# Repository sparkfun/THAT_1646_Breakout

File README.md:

SparkFun THAT 1646 Breakout
========================================

[*BOB-14003*](https://www.sparkfun.com/products/14003)

The THAT 1646 OutSmarts Breakout Board offers an easy solution to adding a balanced audio output to your circuits. The THAT OutSmarts technology has been designed as a high-grade analog line driver and offers a low distortion and high common mode rejection in real-world audio applications. Each breakout board combines the THAT 1646 IC, its supporting components and a ¼" TRS (Tip Ring Sleeve) socket. With these powers combined, you will find it very easy to use the output drivers on breadboards and in projects!

The THAT 1646 OutSmarts Breakout and its sibling, the THAT 1206 InGenius Breakout, perform mirror-image signal conversion. While the InGenius is a balanced-to-unbalanced input receiver, this OutSmarts is an unbalanced-to-balanced output driver. We have made sure to break out each pin you need to utilize the OutSmarts board including the unbalanced input (IN), the positive and negative power supply rails (V+, V-) and, of course, ground (GND). Additionally, adjacent to each leg of the socket are test points for the signal (T, R, S) and normal (TN, RN, SN) contacts.

Repository Contents
-------------------

* **/Hardware** - Eagle design files (.brd, .sch)
* **/Production** - Production panel files (.brd)

Documentation
--------------
* **[Hookup Guide](https://learn.sparkfun.com/tutorials/that-ingenuis-and-outsmarts-breakout-hookup-guide)** - Basic hookup guide for the THAT 1206 and 1646 breakouts.
* **[SparkFun Fritzing repo](https://github.com/sparkfun/Fritzing_Parts)** - Fritzing diagrams for SparkFun products.
* **[SparkFun 3D Model repo](https://github.com/sparkfun/3D_Models)** - 3D models of SparkFun products.

Product Versions
----------------
* [BOB-14003](https://www.sparkfun.com/products/14003) - THAT 1646 OutSmarts breakout board.
* [BOB-14002](https://www.sparkfun.com/products/14002) - The companion THAT 1206 InGenius breakout board.

Version History
---------------
* [V1.0 Tag](https://github.com/sparkfun/THAT_1646_Breakout/commit/2f91aec23e70d395754cfb3aa0515f236956341f) - Files as of product launch.

License Information
-------------------

This product is _**open source**_!

Please review the LICENSE.md file for license information.

If you have any questions or concerns on licensing, please contact techsupport@sparkfun.com.

Distributed as-is; no warranty is given.

- Your friends at SparkFun.

_<COLLABORATION CREDIT>_

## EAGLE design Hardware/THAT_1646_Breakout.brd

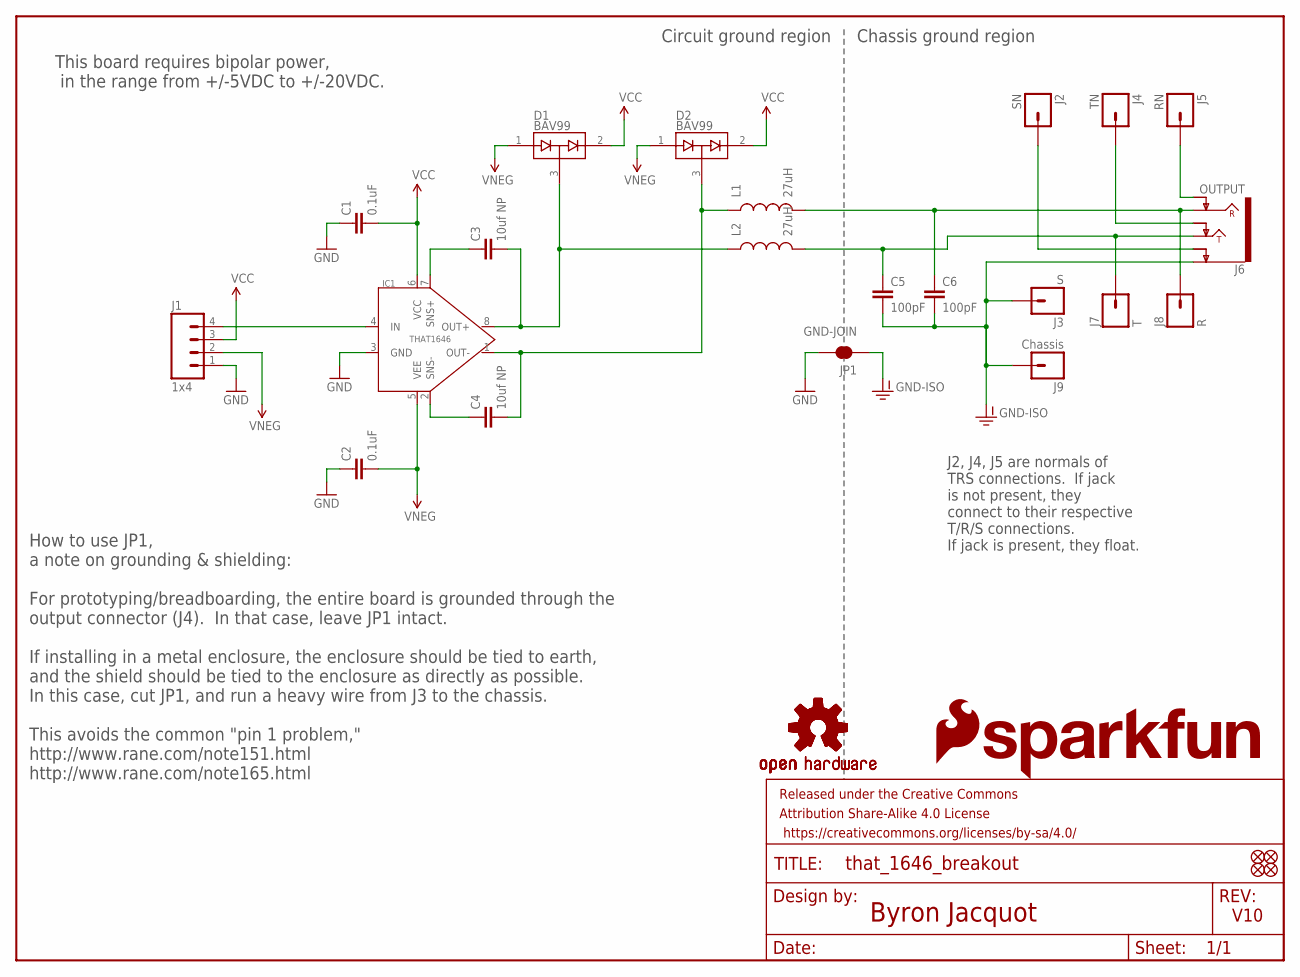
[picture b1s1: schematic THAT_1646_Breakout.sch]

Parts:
C1, C2: 0.1uF; 0603-CAP
C3, C4: 10uf NP; PANASONIC_D
C5, C6: 100pF; 0603-CAP
D1, D2: BAV99; SOT23-3
FD1, FD2, FD3, FD4: FIDUCIALUFIDUCIAL; MICRO-FIDUCIAL
FRAME1: FRAME-LETTER; CREATIVE_COMMONS
IC1: THAT1646; SO08
J1: 1x4; 1X04_NO_SILK_ALL_ROUND
J2: SN; 1X01_NO_SILK
J3: S; 1X01_NO_SILK
J4: TN; 1X01_NO_SILK
J5: RN; 1X01_NO_SILK
J6: OUTPUT; AUDIO_JACK_0.25"_TRS_PTH_RA
J7: T; 1X01_NO_SILK
J8: R; 1X01_NO_SILK
J9: Chassis; 1X01_NO_SILK
JP1: GND-JOIN; PAD-JUMPER-2-NC_BY_TRACE_YES_SILK
L1, L2: 27uH; 0603
LOGO1, LOGO2: OSHW-LOGOS; OSHW-LOGO-S
LOGO4: SFE_LOGO_FLAME.2_INCH; SFE_LOGO_FLAME_.2
LOGO5: SFE_LOGO_NAME.1_INCH; SFE_LOGO_NAME_.1

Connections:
GND: C1.1, C2.1, IC1.3 (GND), J1.1, JP1.2
GND-ISO: C5.2, C6.2, J3.1, J6.SLEEVE (EARTH), J9.1, JP1.1
unnamed: J5.1, J6.RING-NORM
unnamed: J4.1, J6.TIP-NORM
unnamed: J2.1, J6.SLEEVE-NORM (EARTH-NORM)
unnamed: C5.1, J6.TIP, J7.1, L2.2
unnamed: C6.1, J6.RING, J8.1, L1.2
unnamed: C3.- (2), D1.3 (COM), IC1.8 (OUT+), L2.1
unnamed: C4.- (2), D2.3 (COM), IC1.1 (OUT-), L1.1
unnamed: C4.+ (1), IC1.2 (SNS-)
unnamed: C3.+ (1), IC1.7 (SNS+)
unnamed: IC1.4 (IN), J1.4
VCC: C1.2, D1.2 (C2), D2.2 (C2), IC1.6 (VCC), J1.3
VNEG: C2.2, D1.1 (A1), D2.1 (A1), IC1.5 (VEE), J1.2

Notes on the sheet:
Byron Jacquot
V10
Chassis ground region
Circuit ground region
How to use JP1, a note on grounding & shielding: For prototyping/breadboarding, the entire board is grounded through the output connector (J4). In that case, leave JP1 intact. If installing in a metal enclosure, the enclosure should be tied to earth, and the shield should be tied to the enclosure a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
This board requires bipolar power, in the range from +/-5VDC to +/-20VDC.
J2, J4, J5 are normals of TRS connections. If jack is not present, they connect to their respective T/R/S connections. If jack is present, they float.

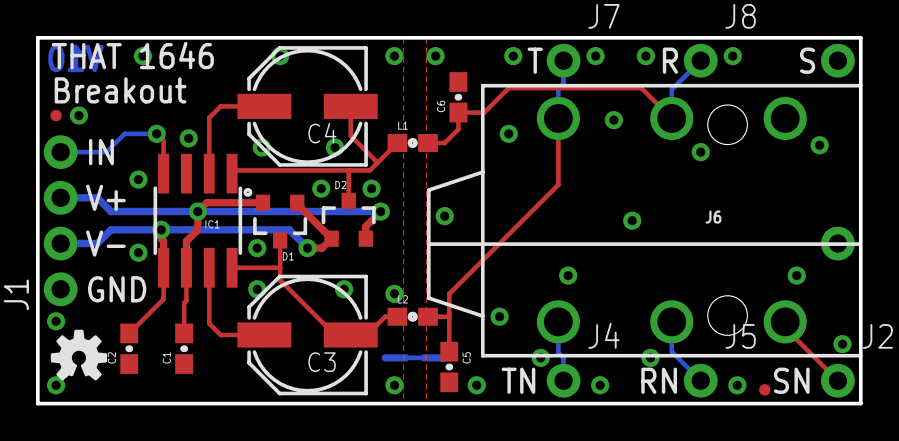
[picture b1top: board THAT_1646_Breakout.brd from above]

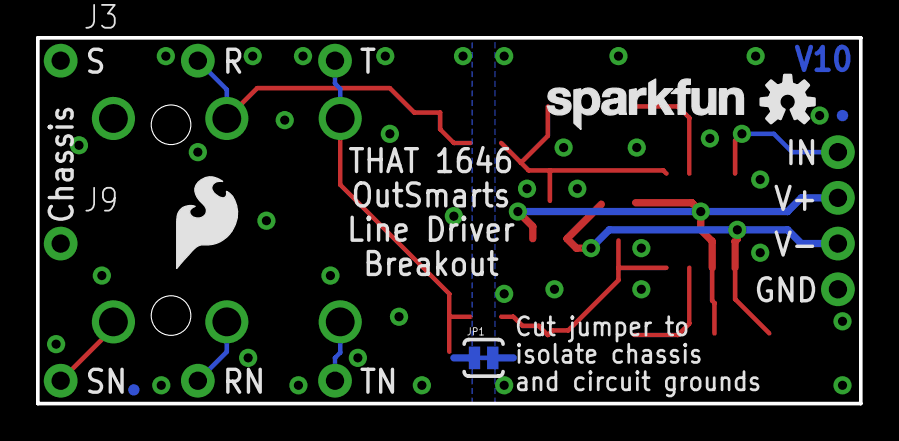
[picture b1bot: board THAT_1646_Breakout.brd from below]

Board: 2 copper layers, 45.7 x 20.3 mm, 30 parts (8 on the bottom side), 14 nets.

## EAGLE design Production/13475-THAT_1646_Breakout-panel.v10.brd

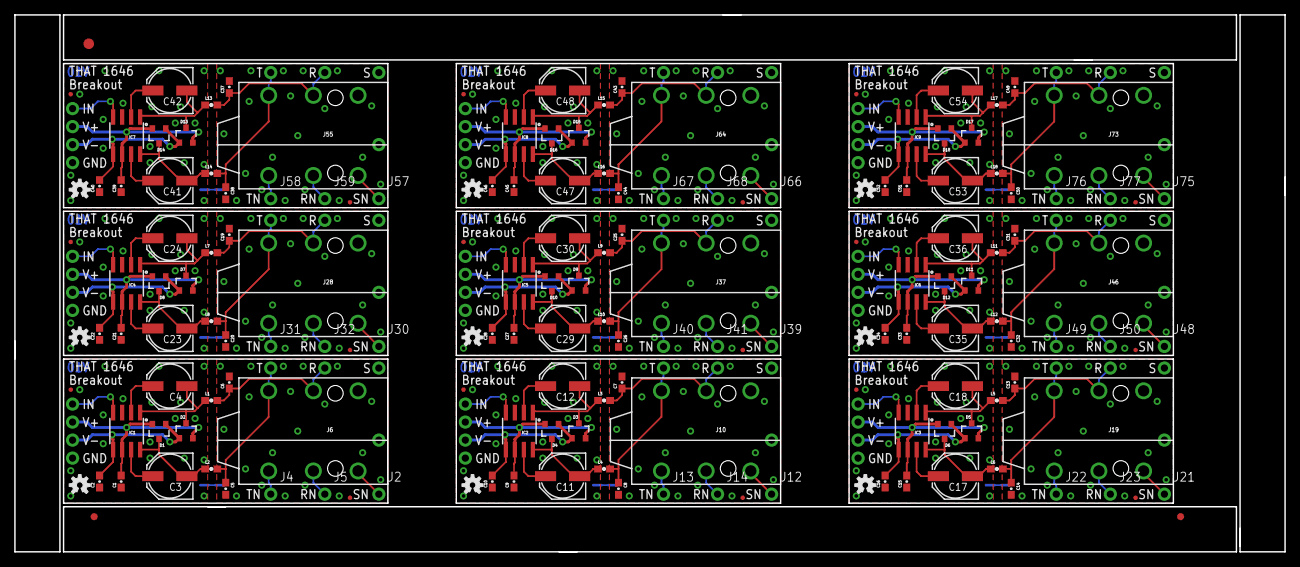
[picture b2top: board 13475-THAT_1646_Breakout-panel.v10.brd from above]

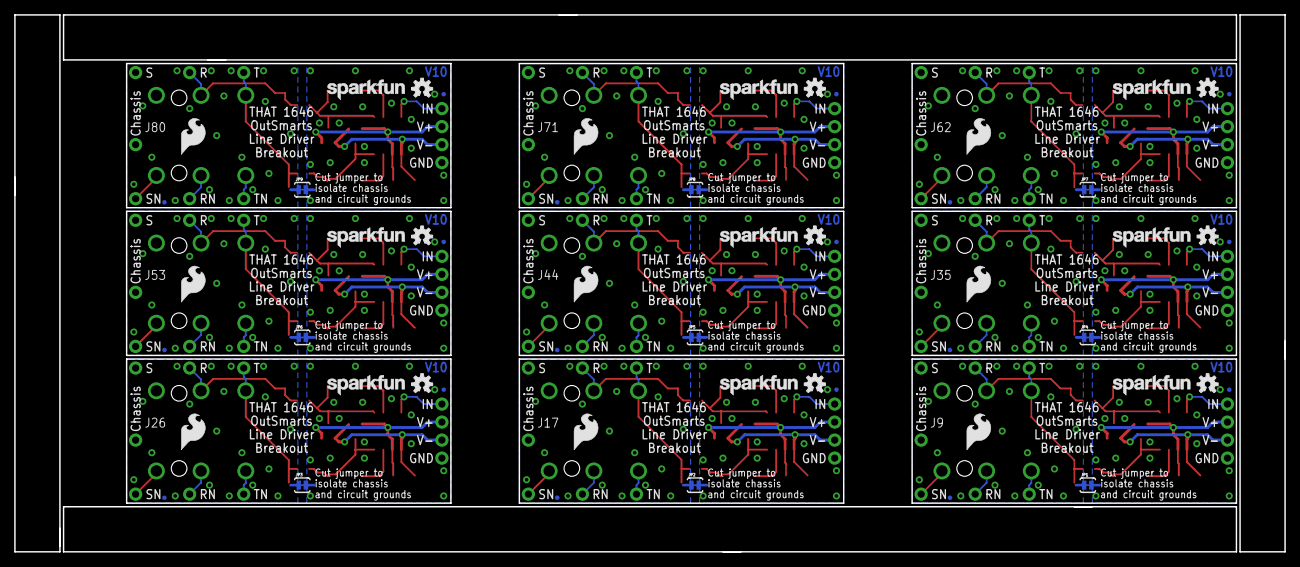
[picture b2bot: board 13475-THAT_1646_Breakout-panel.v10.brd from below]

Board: 2 copper layers, 179.1 x 75.7 mm, 264 parts (72 on the bottom side), 126 nets.

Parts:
C1, C2, C9, C10, C15, C16, C21, C22, C27, C28, C33, C34, C39, C40, C45, C46, C51, C52: 0.1uF; 0603-CAP
C3, C4, C11, C12, C17, C18, C23, C24, C29, C30, C35, C36, C41, C42, C47, C48, C53, C54: 10uf NP; PANASONIC_D
C5, C6, C7, C8, C13, C14, C19, C20, C25, C26, C31, C32, C37, C38, C43, C44, C49, C50: 100pF; 0603-CAP
D1, D2, D3, D4, D5, D6, D7, D8, D9, D10, D11, D12, D13, D14, D15, D16, D17, D18: BAV99; SOT23-3
E$1: FIDUCIAL-1.5X3
E$3, E$4: FIDUCIAL-1X2
FD1, FD2, FD3, FD4, FD5, FD6, FD7, FD8, FD9, FD10, FD11, FD12, FD13, FD14, FD15, FD16, FD17, FD18, FD19, FD20, FD21, FD22, FD23, FD24, FD25, FD26, FD27, FD28, FD29, FD30, FD31, FD32, FD33, FD34, FD35, FD36: FIDUCIALUFIDUCIAL; MICRO-FIDUCIAL
IC1, IC2, IC3, IC4, IC5, IC6, IC7, IC8, IC9: THAT1646; SO08
J1, J11, J20, J29, J38, J47, J56, J65, J74: 1x4; 1X04_NO_SILK_ALL_ROUND
J2, J12, J21, J30, J39, J48, J57, J66, J75: SN; 1X01_NO_SILK
J3, J18, J27, J36, J45, J54, J63, J72, J81: S; 1X01_NO_SILK
J4, J13, J22, J31, J40, J49, J58, J67, J76: TN; 1X01_NO_SILK
J5, J14, J23, J32, J41, J50, J59, J68, J77: RN; 1X01_NO_SILK
J6, J10, J19, J28, J37, J46, J55, J64, J73: OUTPUT; AUDIO_JACK_0.25"_TRS_PTH_RA
J7, J15, J24, J33, J42, J51, J60, J69, J78: T; 1X01_NO_SILK
J8, J16, J25, J34, J43, J52, J61, J70, J79: R; 1X01_NO_SILK
J9, J17, J26, J35, J44, J53, J62, J71, J80: Chassis; 1X01_NO_SILK
JP1, JP2, JP3, JP4, JP5, JP6, JP7, JP8, JP9: GND-JOIN; PAD-JUMPER-2-NC_BY_TRACE_YES_SILK
L1, L2, L3, L4, L5, L6, L7, L8, L9, L10, L11, L12, L13, L14, L15, L16, L17, L18: 27uH; 0603
LOGO1, LOGO2, LOGO6, LOGO7, LOGO10, LOGO11, LOGO14, LOGO15, LOGO18, LOGO19, LOGO22, LOGO23, LOGO26, LOGO27, LOGO30, LOGO31, LOGO34, LOGO35: OSHW-LOGOS; OSHW-LOGO-S
LOGO3, LOGO5, LOGO9, LOGO13, LOGO17, LOGO21, LOGO25, LOGO29, LOGO33: SFE_LOGO_NAME.1_INCH; SFE_LOGO_NAME_.1
LOGO4, LOGO8, LOGO12, LOGO16, LOGO20, LOGO24, LOGO28, LOGO32, LOGO36: SFE_LOGO_FLAME.2_INCH; SFE_LOGO_FLAME_.2

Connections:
GND: C1.1, C2.1, IC1.3, J1.1, JP1.2
GND1: C9.1, C10.1, IC2.3, J11.1, JP2.2
GND2: C15.1, C16.1, IC3.3, J20.1, JP3.2
GND3: C21.1, C22.1, IC4.3, J29.1, JP4.2
GND4: C27.1, C28.1, IC5.3, J38.1, JP5.2
GND5: C33.1, C34.1, IC6.3, J47.1, JP6.2
GND6: C39.1, C40.1, IC7.3, J56.1, JP7.2
GND7: C45.1, C46.1, IC8.3, J65.1, JP8.2
GND8: C51.1, C52.1, IC9.3, J74.1, JP9.2
GND-ISO: C5.2, C6.2, J3.1, J6.SLEEVE, J9.1, JP1.1
GND-ISO1: C7.2, C8.2, J10.SLEEVE, J17.1, J18.1, JP2.1
GND-ISO2: C13.2, C14.2, J19.SLEEVE, J26.1, J27.1, JP3.1
GND-ISO3: C19.2, C20.2, J28.SLEEVE, J35.1, J36.1, JP4.1
GND-ISO4: C25.2, C26.2, J37.SLEEVE, J44.1, J45.1, JP5.1
GND-ISO5: C31.2, C32.2, J46.SLEEVE, J53.1, J54.1, JP6.1
GND-ISO6: C37.2, C38.2, J55.SLEEVE, J62.1, J63.1, JP7.1
GND-ISO7: C43.2, C44.2, J64.SLEEVE, J71.1, J72.1, JP8.1
GND-ISO8: C49.2, C50.2, J73.SLEEVE, J80.1, J81.1, JP9.1
unnamed: J5.1, J6.RING-NORM
unnamed: J4.1, J6.TIP-NORM
unnamed: J2.1, J6.SLEEVE-NORM
unnamed: C8.1, J10.TIP, J15.1, L4.2
unnamed: C7.1, J10.RING, J16.1, L3.2
unnamed: C11.-, D4.3, IC2.8, L4.1
unnamed: C12.-, D3.3, IC2.1, L3.1
unnamed: C5.1, J6.TIP, J7.1, L2.2
unnamed: C6.1, J6.RING, J8.1, L1.2
unnamed: C3.-, D1.3, IC1.8, L2.1
unnamed: C4.-, D2.3, IC1.1, L1.1
unnamed: C12.+, IC2.2
unnamed: C4.+, IC1.2
unnamed: C3.+, IC1.7
unnamed: C11.+, IC2.7
unnamed: IC1.4, J1.4
unnamed: IC2.4, J11.4
unnamed: J10.RING-NORM, J14.1
unnamed: J10.TIP-NORM, J13.1
unnamed: J10.SLEEVE-NORM, J12.1
unnamed: C14.1, J19.TIP, J24.1, L6.2
unnamed: C13.1, J19.RING, J25.1, L5.2
unnamed: C17.-, D6.3, IC3.8, L6.1
unnamed: C18.-, D5.3, IC3.1, L5.1
unnamed: C18.+, IC3.2
unnamed: C17.+, IC3.7
unnamed: IC3.4, J20.4
unnamed: J19.RING-NORM, J23.1
unnamed: J19.TIP-NORM, J22.1
unnamed: J19.SLEEVE-NORM, J21.1
unnamed: C20.1, J28.TIP, J33.1, L8.2
unnamed: C19.1, J28.RING, J34.1, L7.2
unnamed: C23.-, D8.3, IC4.8, L8.1
unnamed: C24.-, D7.3, IC4.1, L7.1
unnamed: C24.+, IC4.2
unnamed: C23.+, IC4.7
unnamed: IC4.4, J29.4
unnamed: J28.RING-NORM, J32.1
unnamed: J28.TIP-NORM, J31.1
unnamed: J28.SLEEVE-NORM, J30.1
unnamed: C26.1, J37.TIP, J42.1, L10.2
unnamed: C25.1, J37.RING, J43.1, L9.2
unnamed: C29.-, D10.3, IC5.8, L10.1
unnamed: C30.-, D9.3, IC5.1, L9.1
unnamed: C30.+, IC5.2
unnamed: C29.+, IC5.7
unnamed: IC5.4, J38.4
unnamed: J37.RING-NORM, J41.1
unnamed: J37.TIP-NORM, J40.1
unnamed: J37.SLEEVE-NORM, J39.1
unnamed: C32.1, J46.TIP, J51.1, L12.2
unnamed: C31.1, J46.RING, J52.1, L11.2
unnamed: C35.-, D12.3, IC6.8, L12.1
unnamed: C36.-, D11.3, IC6.1, L11.1
unnamed: C36.+, IC6.2
unnamed: C35.+, IC6.7
unnamed: IC6.4, J47.4
unnamed: J46.RING-NORM, J50.1
unnamed: J46.TIP-NORM, J49.1
unnamed: J46.SLEEVE-NORM, J48.1
unnamed: C38.1, J55.TIP, J60.1, L14.2
unnamed: C37.1, J55.RING, J61.1, L13.2
unnamed: C41.-, D14.3, IC7.8, L14.1
unnamed: C42.-, D13.3, IC7.1, L13.1
unnamed: C42.+, IC7.2
unnamed: C41.+, IC7.7
unnamed: IC7.4, J56.4
unnamed: J55.RING-NORM, J59.1
unnamed: J55.TIP-NORM, J58.1
unnamed: J55.SLEEVE-NORM, J57.1
unnamed: C44.1, J64.TIP, J69.1, L16.2
unnamed: C43.1, J64.RING, J70.1, L15.2
unnamed: C47.-, D16.3, IC8.8, L16.1
unnamed: C48.-, D15.3, IC8.1, L15.1
unnamed: C48.+, IC8.2
unnamed: C47.+, IC8.7
unnamed: IC8.4, J65.4
unnamed: J64.RING-NORM, J68.1
unnamed: J64.TIP-NORM, J67.1
unnamed: J64.SLEEVE-NORM, J66.1
unnamed: C50.1, J73.TIP, J78.1, L18.2
unnamed: C49.1, J73.RING, J79.1, L17.2
unnamed: C53.-, D18.3, IC9.8, L18.1
unnamed: C54.-, D17.3, IC9.1, L17.1
unnamed: C54.+, IC9.2
unnamed: C53.+, IC9.7
unnamed: IC9.4, J74.4
unnamed: J73.RING-NORM, J77.1
unnamed: J73.TIP-NORM, J76.1
unnamed: J73.SLEEVE-NORM, J75.1
VCC: C1.2, D1.2, D2.2, IC1.6, J1.3
VCC1: C9.2, D3.2, D4.2, IC2.6, J11.3
VCC2: C15.2, D5.2, D6.2, IC3.6, J20.3
VCC3: C21.2, D7.2, D8.2, IC4.6, J29.3
VCC4: C27.2, D9.2, D10.2, IC5.6, J38.3
VCC5: C33.2, D11.2, D12.2, IC6.6, J47.3
VCC6: C39.2, D13.2, D14.2, IC7.6, J56.3
VCC7: C45.2, D15.2, D16.2, IC8.6, J65.3
VCC8: C51.2, D17.2, D18.2, IC9.6, J74.3
VNEG: C2.2, D1.1, D2.1, IC1.5, J1.2
VNEG1: C10.2, D3.1, D4.1, IC2.5, J11.2
VNEG2: C16.2, D5.1, D6.1, IC3.5, J20.2
VNEG3: C22.2, D7.1, D8.1, IC4.5, J29.2
VNEG4: C28.2, D9.1, D10.1, IC5.5, J38.2
VNEG5: C34.2, D11.1, D12.1, IC6.5, J47.2
VNEG6: C40.2, D13.1, D14.1, IC7.5, J56.2
VNEG7: C46.2, D15.1, D16.1, IC8.5, J65.2
VNEG8: C52.2, D17.1, D18.1, IC9.5, J74.2

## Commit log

2016-07-27 Initial checkin of boilerplate empty repo.
2016-07-27 Moving in 1646 files.
    They were previously in the 1206 repo.
2016-07-27 Routed board.
    Worked through initial checklist.
2016-08-08 Post-review updates.
2016-08-09 Updates from engineering checklist.
2016-08-09 Addressing Kade's checklist issues.
    -Via under "THAT" in top silk
    -Nixing "Toed"
    -90-deg trace on bottom made 45.
    -Moved chassis connection out from under TRS.
2016-08-09 One last checklist issue.
2017-01-09 Adding testpoints on T/R/S connections.
2017-01-09 Moving PTH holes to 0.1 grid.
2017-01-16 Updating .gitignore to ignore spice temp files.
2017-01-16 Updates after group review.
    -Chassis ground pad moved away from selective solder runout.
    -Version numbers fixed.
    -Top/bottom fiducials co-located.
    -Flame oriented to match text.
2017-01-17 Updates from engineering checklist.
    Found too-narrow silk in some packages.
2017-01-17 Engineering checklist updates.
    Found too narrow silk in some packages.
    Moves a couple vias out from under silk text.
2017-01-27 panel
2017-03-31 Repo cleanup for release.
    Deleted empty directories.
    Updated readme file.
2017-03-31 Fixing grounding note in schem.
    J9 is the pad to use for chassis ground. It was incorrectly notated as
    J3.

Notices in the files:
parts and their libraries:
SparkFun-DiscreteSemi: Licensing: Creative Commons ShareAlike 4.0 International - https://creativecommons.org/licenses/by-sa/4.0
SparkFun-Aesthetics: Released under the Creative Commons Attribution Share-Alike 4.0 License
SparkFun-Aesthetics: https://creativecommons.org/licenses/by-sa/4.0
